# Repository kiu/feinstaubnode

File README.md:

# feinstaubnode

First try at using KiCAD.

https://schoar.de/tinkering/feinstaubnode

http://luftdaten.info/

# ERRATA
REV A: TX und RX sind vertauscht. Kann im Verbindungskabel entsprechend geändert werden.

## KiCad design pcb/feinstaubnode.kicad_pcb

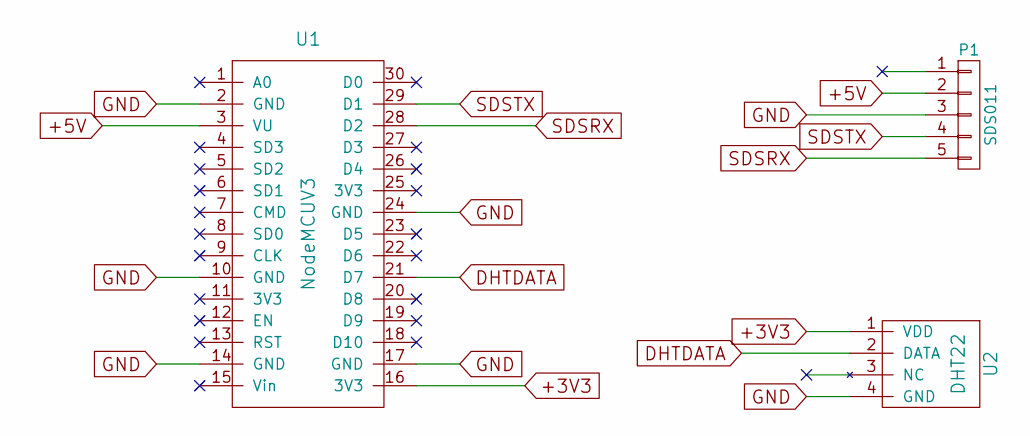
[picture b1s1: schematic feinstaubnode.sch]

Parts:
P1: SDS011; Pin_Header_Angled_1x05_Pitch2.54mm
U1: NodeMCUV3; NodeMCUV3-NoHoles
U2: DHT22; TO-220-4_Vertical

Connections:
+3V3: U1.16 (3V3), U2.1 (VDD)
+5V: P1.2, U1.3 (VU)
DHTDATA: U1.21 (D7), U2.2 (DATA)
GND: P1.3, U1.2 (GND), U1.10 (GND), U1.14 (GND), U1.17 (GND), U1.24 (GND), U2.4 (GND)
SDSRX: P1.5, U1.28 (D2)
SDSTX: P1.4, U1.29 (D1)

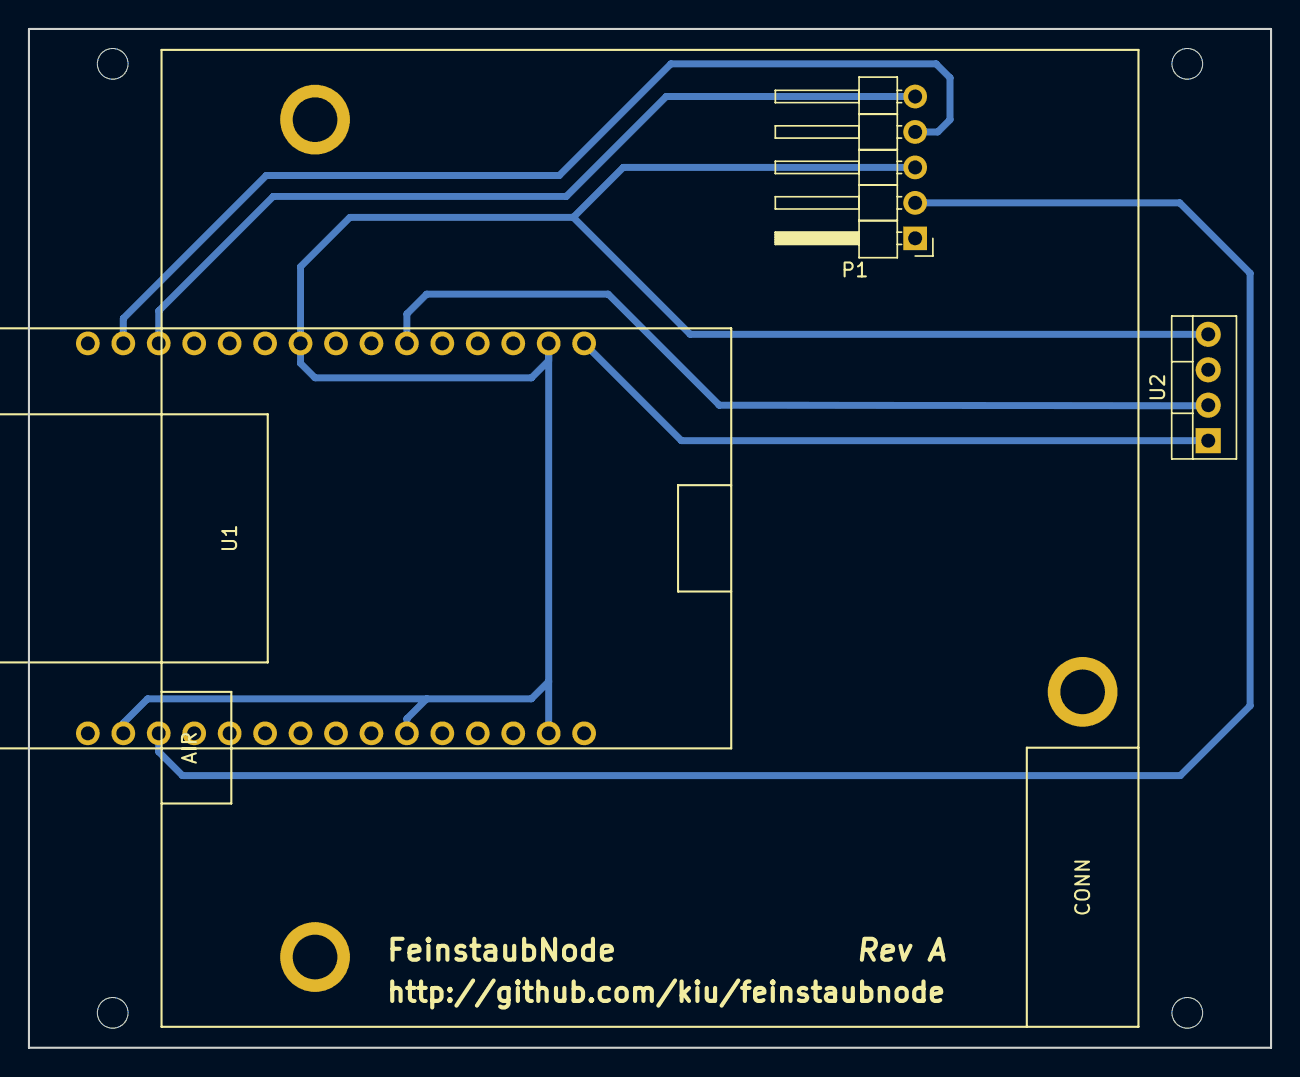
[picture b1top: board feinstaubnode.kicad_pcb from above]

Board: 2 copper layers, 89.0 x 73.0 mm, 3 parts (0 on the bottom side), 6 nets.

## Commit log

2017-02-25 Datasheets of components
2017-02-25 git ignore
2017-03-17 Initial Rev
    REV A
2017-03-17 typo
